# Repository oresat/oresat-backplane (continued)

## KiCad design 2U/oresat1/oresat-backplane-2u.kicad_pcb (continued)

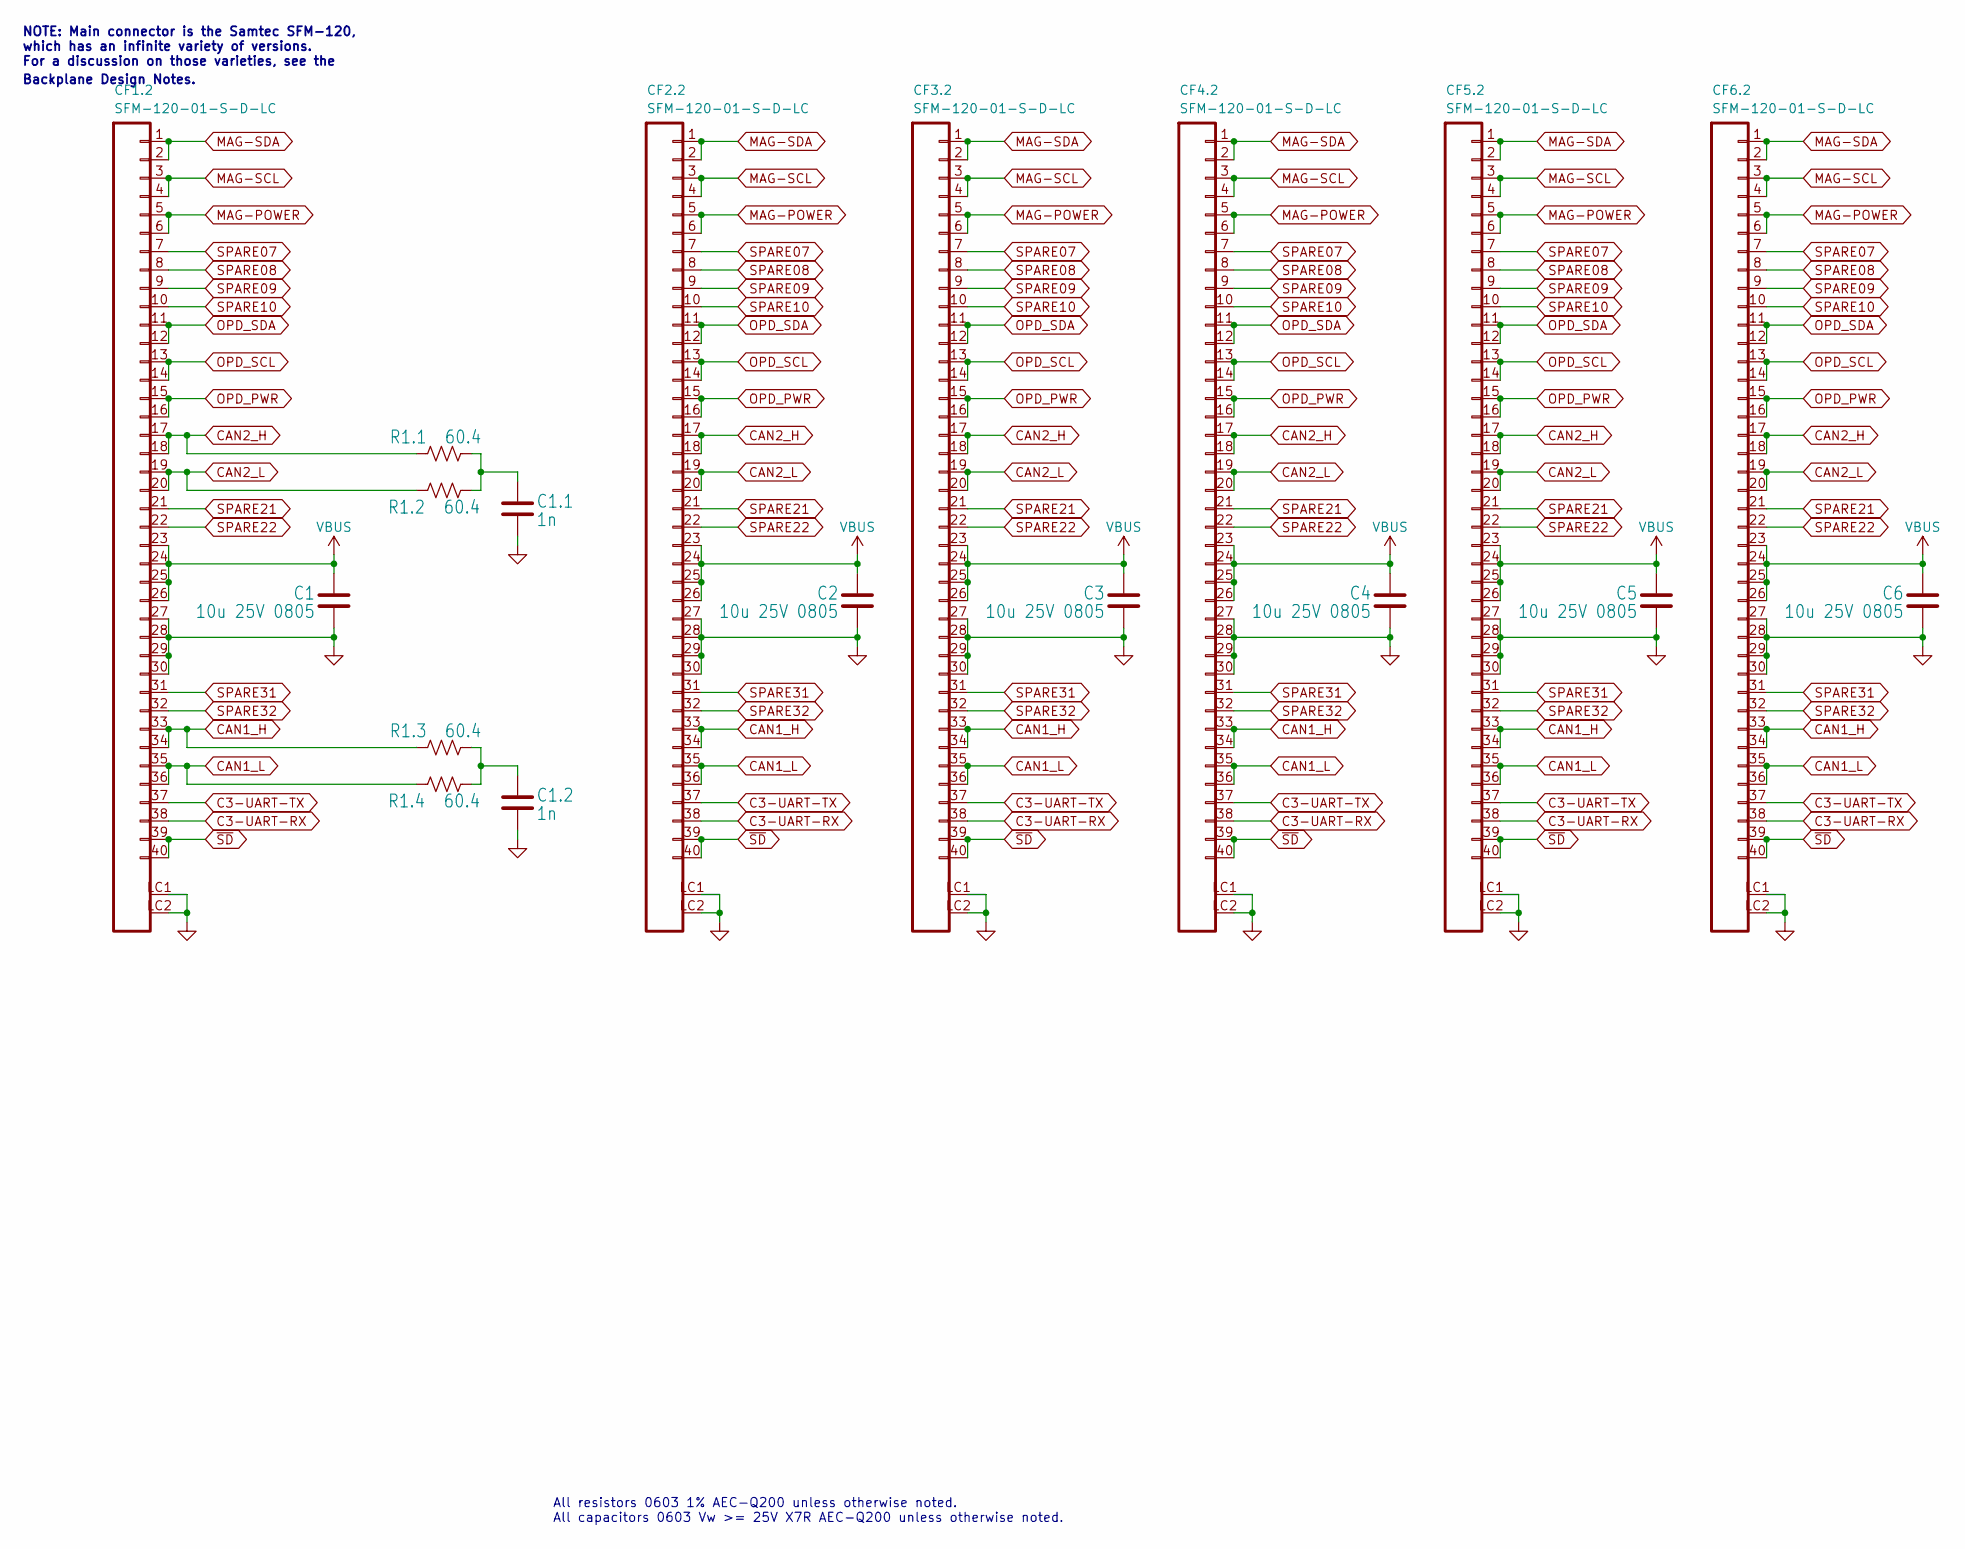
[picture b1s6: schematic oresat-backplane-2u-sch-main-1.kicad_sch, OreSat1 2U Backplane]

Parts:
C1, C2, C3, C4, C5, C6: 10u 25V 0805; C_1206_3216Metric; MPN GRT31CR71E106KE13L
C1.1, C1.2: 1n; 0603-C-NOSILK; MPN C0603C102J5GECAUTO
CF1.2, CF2.2, CF3.2, CF4.2, CF5.2, CF6.2: SFM-120-01-S-D-LC; J-SAMTEC-SFM-120-X1-XXX-D; MPN SFM-120-01-S-D-LC
R1.1, R1.2, R1.3, R1.4: 60.4; R_1206_3216Metric; MPN RMCF1206FT60R4

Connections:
C3-UART-RX: CF1.2.38, CF2.2.38, CF3.2.38, CF4.2.38, CF5.2.38, CF6.2.38; also elsewhere on the board
C3-UART-TX: CF1.2.37, CF2.2.37, CF3.2.37, CF4.2.37, CF5.2.37, CF6.2.37; also elsewhere on the board
CAN1_H: CF1.2.33, CF1.2.34, CF2.2.33, CF2.2.34, CF3.2.33, CF3.2.34, CF4.2.33, CF4.2.34, CF5.2.33, CF5.2.34, CF6.2.33, CF6.2.34, R1.3.2; also elsewhere on the board
CAN1_L: CF1.2.35, CF1.2.36, CF2.2.35, CF2.2.36, CF3.2.35, CF3.2.36, CF4.2.35, CF4.2.36, CF5.2.35, CF5.2.36, CF6.2.35, CF6.2.36, R1.4.1; also elsewhere on the board
CAN2_H: CF1.2.17, CF1.2.18, CF2.2.17, CF2.2.18, CF3.2.17, CF3.2.18, CF4.2.17, CF4.2.18, CF5.2.17, CF5.2.18, CF6.2.17, CF6.2.18, R1.1.2; also elsewhere on the board
CAN2_L: CF1.2.19, CF1.2.20, CF2.2.19, CF2.2.20, CF3.2.19, CF3.2.20, CF4.2.19, CF4.2.20, CF5.2.19, CF5.2.20, CF6.2.19, CF6.2.20, R1.2.1; also elsewhere on the board
GND: C1.2, C1.1.2, C1.2.2, C2.2, C3.2, C4.2, C5.2, C6.2, CF1.2.27, CF1.2.28, CF1.2.29, CF1.2.30, CF1.2.LC1, CF1.2.LC2, CF2.2.27, CF2.2.28, CF2.2.29, CF2.2.30, CF2.2.LC1, CF2.2.LC2, CF3.2.27, CF3.2.28, CF3.2.29, CF3.2.30, CF3.2.LC1, CF3.2.LC2, CF4.2.27, CF4.2.28, CF4.2.29, CF4.2.30, CF4.2.LC1, CF4.2.LC2, CF5.2.27, CF5.2.28, CF5.2.29, CF5.2.30, CF5.2.LC1, CF5.2.LC2, CF6.2.27, CF6.2.28, CF6.2.29, CF6.2.30, CF6.2.LC1, CF6.2.LC2; also elsewhere on the board
MAG-POWER: CF1.2.5, CF1.2.6, CF2.2.5, CF2.2.6, CF3.2.5, CF3.2.6, CF4.2.5, CF4.2.6, CF5.2.5, CF5.2.6, CF6.2.5, CF6.2.6; also elsewhere on the board
MAG-SCL: CF1.2.3, CF1.2.4, CF2.2.3, CF2.2.4, CF3.2.3, CF3.2.4, CF4.2.3, CF4.2.4, CF5.2.3, CF5.2.4, CF6.2.3, CF6.2.4; also elsewhere on the board
MAG-SDA: CF1.2.1, CF1.2.2, CF2.2.1, CF2.2.2, CF3.2.1, CF3.2.2, CF4.2.1, CF4.2.2, CF5.2.1, CF5.2.2, CF6.2.1, CF6.2.2; also elsewhere on the board
unnamed: C1.1.1, R1.1.1, R1.2.2
unnamed: C1.2.1, R1.3.1, R1.4.2
OPD_PWR: CF1.2.15, CF1.2.16, CF2.2.15, CF2.2.16, CF3.2.15, CF3.2.16, CF4.2.15, CF4.2.16, CF5.2.15, CF5.2.16, CF6.2.15, CF6.2.16; also elsewhere on the board
OPD_SCL: CF1.2.13, CF1.2.14, CF2.2.13, CF2.2.14, CF3.2.13, CF3.2.14, CF4.2.13, CF4.2.14, CF5.2.13, CF5.2.14, CF6.2.13, CF6.2.14; also elsewhere on the board
OPD_SDA: CF1.2.11, CF1.2.12, CF2.2.11, CF2.2.12, CF3.2.11, CF3.2.12, CF4.2.11, CF4.2.12, CF5.2.11, CF5.2.12, CF6.2.11, CF6.2.12; also elsewhere on the board
SPARE07: CF1.2.7, CF2.2.7, CF3.2.7, CF4.2.7, CF5.2.7, CF6.2.7; also elsewhere on the board
SPARE08: CF1.2.8, CF2.2.8, CF3.2.8, CF4.2.8, CF5.2.8, CF6.2.8; also elsewhere on the board
SPARE09: CF1.2.9, CF2.2.9, CF3.2.9, CF4.2.9, CF5.2.9, CF6.2.9; also elsewhere on the board
SPARE10: CF1.2.10, CF2.2.10, CF3.2.10, CF4.2.10, CF5.2.10, CF6.2.10; also elsewhere on the board
SPARE21: CF1.2.21, CF2.2.21, CF3.2.21, CF4.2.21, CF5.2.21, CF6.2.21; also elsewhere on the board
SPARE22: CF1.2.22, CF2.2.22, CF3.2.22, CF4.2.22, CF5.2.22, CF6.2.22; also elsewhere on the board
SPARE31: CF1.2.31, CF2.2.31, CF3.2.31, CF4.2.31, CF5.2.31, CF6.2.31; also elsewhere on the board
SPARE32: CF1.2.32, CF2.2.32, CF3.2.32, CF4.2.32, CF5.2.32, CF6.2.32; also elsewhere on the board
VBUS: C1.1, C2.1, C3.1, C4.1, C5.1, C6.1, CF1.2.23, CF1.2.24, CF1.2.25, CF1.2.26, CF2.2.23, CF2.2.24, CF2.2.25, CF2.2.26, CF3.2.23, CF3.2.24, CF3.2.25, CF3.2.26, CF4.2.23, CF4.2.24, CF4.2.25, CF4.2.26, CF5.2.23, CF5.2.24, CF5.2.25, CF5.2.26, CF6.2.23, CF6.2.24, CF6.2.25, CF6.2.26; also elsewhere on the board
~SD: CF1.2.39, CF1.2.40, CF2.2.39, CF2.2.40, CF3.2.39, CF3.2.40, CF4.2.39, CF4.2.40, CF5.2.39, CF5.2.40, CF6.2.39, CF6.2.40; also elsewhere on the board

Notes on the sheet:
NOTE: Main connector is the Samtec SFM-120, which has an infinite variety of versions. For a discussion on those varieties, see the
All resistors 0603 1% AEC-Q200 unless otherwise noted. All capacitors 0603 Vw >= 25V X7R AEC-Q200 unless otherwise noted.
Backplane Design Notes.

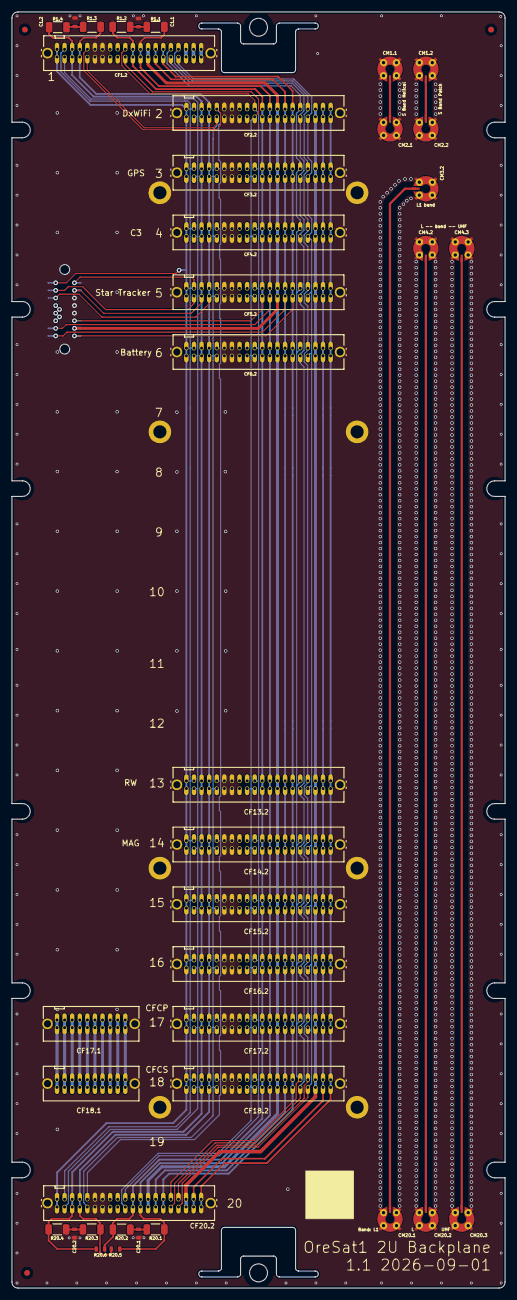
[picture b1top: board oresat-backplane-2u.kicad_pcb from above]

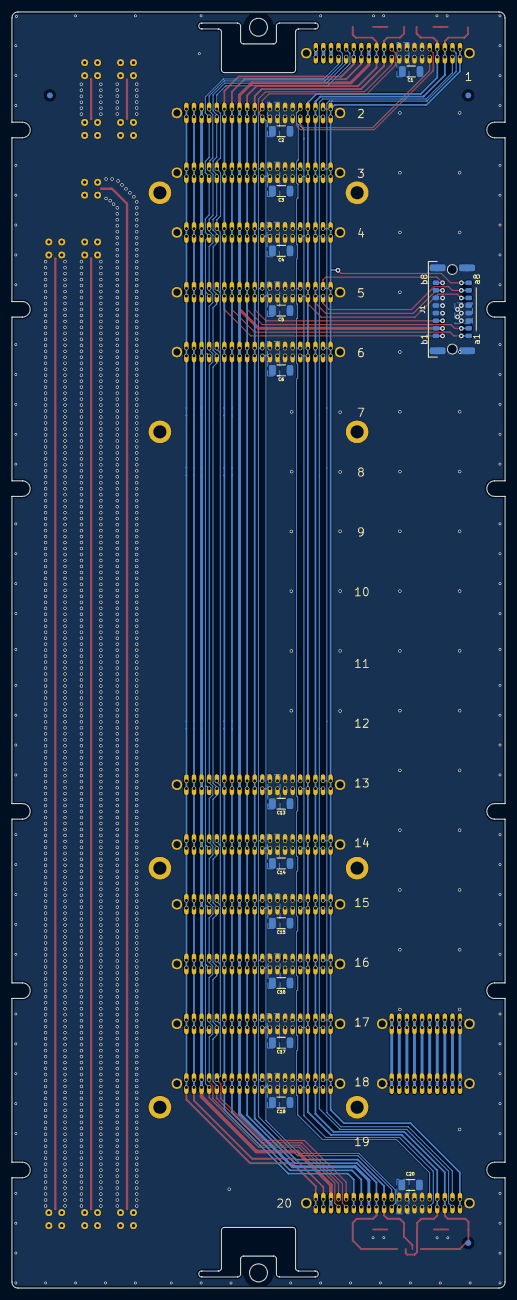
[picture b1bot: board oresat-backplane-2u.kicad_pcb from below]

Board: 4 copper layers, 82.5 x 213.5 mm, 69 parts (17 on the bottom side), 42 nets.

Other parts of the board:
PH1, PH2: MountingHole_3mm

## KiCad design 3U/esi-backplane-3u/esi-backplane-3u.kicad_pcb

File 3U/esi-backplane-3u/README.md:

---
title: "**ESI/OreSat 3U Backplane Fabrication and Assembly Information**"
subtitle: |
  **Fabrication and Assembly Information**\
  For build TIME-STAMP
fontsize: 10pt
geometry:
  - margin=0.5in
toc: true
toc-depth: 2
colorlinks: true
urlcolor: blue
---

\newpage

# About this Board

## Board Description

The ESI/OreSat 3U Backplane is the backplane for a 3U backplane based on the open source [OreSat CubeSat system](https://www.oresat.org/). The backplane has:

- 40 pin main connnectors for Oresat-based cards
- Bus voltage (2S Lithium Ion batteries with a Vnom of 7.2V)
- Two CAN busses for inter-card communication
- RF lines using SMPM RF connectors and microstrips
- A debug connector to carry critical lines to the outside of the CubeSat
- Four cutouts for solar module connections

## Documentation Links

- OreSat Backplane hardware Git repository: <https://github.com/oresat/oresat-backplane>
- **TODO:** Backplane Design Notes + Design Review Notes

## Documentation Files

| Filename                        | Notes                                    |
| ------------------------------- | ---------------------------------------- |
| README.pdf                      | This README file                         |
| PROJECT-NAME-outline.dxf        | Board outline (with holes) in DXF format |
| PROJECT-NAME-pcba.step          | 3D model of PCBA (with components)       |
| PROJECT-NAME-render-bot.jpg     | Render of the top of the 3D model        |
| PROJECT-NAME-render-bot.jpg     | Render of the bottom of the 3D model     |
| PROJECT-NAME-schematic.pdf      | PDF of board schematics                  |

## Contact Information

- Website: <https://www.oresat.org/>
- Email: <oresat@pdx.edu>
- Instagram: @pdxaerospace

## Board Renders

{width=50%}
{width=50%}

\newpage

# Printed Circuit Board (PCB) Fabrication Information

## Board Info

- 4 layer board
- Bounding box is 82.5 x 327.0 mm
- Board thickness is 1.59 mm (0.063 inch)
- **Important:** See Materials and Stack Up sections below

## Board Requirements

- Design Rules
    - Minimum Trace / Space design rules
       - Outer layers: 0.127 mm (5.0 mil) / 0.127 mm (5.0 mil)
       - Inner layers: 0.127 mm (5.0 mil) / 0.127 mm (5.0 mil)
    - Outer dimension router tolerance: +/- 0.254 mm (10.0 mil)
    - Hole placement tolerance: +/- 0.075 mm (3.0 mil)
    - Inner tab routed slot tolerance: +/- 0.254 mm (10.0 mil)
- Drills
   - Drill Positional Tolerance: 0.051 mm (2.0 mil)
   - Drill Size tolerance: +/- 0.064 mm (2.5 mil)
- Plated/Un-plated holes
  - There are 4 un-plated (NPT) holes
  - PTH minimum diameter: 0.254 mm (10 mil)
  - PTH minimum annulus: 0.102 mm (4 mil) radius
- Outline/Routing
  - Requires a 1.0 mm or smaller diameter routing bit
- Slots
  - There are no slots (although two cutouts have slot-like features)
- Cutouts
  - There are five cutouts.
- There are 3 fiducials on the top layer and 3 fiducials on the bottom layer.
- Panel tabs ("mouse bites")
   - Card edges must be smooth; no mouse bites or other intrusions into the card outline.
   - If external mouse bites are required, minimize and customer will remove by hand before assembly.
- If not otherwise specified, build to IPC 6012 Class 2 or better.

## Materials

- Controlled impedance
   - The stackup is critical for the performance of high speed signals on this board.
   - As long as the stackup is controlled, the board is not considered controlled impedance.
- Isola FR408HR or material with equivalent Dk.
- Board Surface treatment should be ENIG, althogh immersion Silver is acceptable.
- White silkscreen on top and bottom surface
- Taiyo PSR-4000 or equivalent soldermask on top and bottom, no requirements for color.

## Stack Up

| Layer         | Thickness           | Notes                                        |
|---------------|---------------------|----------------------------------------------|
| Top Copper    | 0.043 mm /  1.7 mil |  Layer 1 foil, 1 oz Cu after plating         |
| prepreg       | 0.200 mm /  7.9 mil |  Prepreg - Isola FR408HR 2113                |
| Layer 2       | 0.018 mm /  0.7 mil |  Layer 2 foil, 0.5 oz Cu                     |
| Core          | 0.991 mm /   39 mil |  Core Isola FR408HR                          |
| Layer 3       | 0.018 mm /  0.7 mil |  Layer 3 foil, 0.5 oz Cu                     |
| prepreg       | 0.200 mm /  7.9 mil |  Prepreg - Isola FR408HR 2113                |
| Bottom Copper | 0.043 mm /  1.7 mil |  Layer 4 foil, 1 oz copper after plating     |
| **Total Stackup** | **1.588 mm / 62.5 mil** |                                      |

## Array / Panel Information

- Coordinate with Contract Manufacturer (CM) for optimal size of this panel.
- If no feedback from CM, then produce single boards (no panel).

## Fabrication Files

### IPC-2581 File

| Filename                 | Notes                                   |
| ------------------------ | --------------------------------------- |
| PROJECT-NAME-ipc2581.xml | IPC-2581 board information file         |

### Legacy PCB Files

| Filename                      | Notes                                         |
| ------------------------------| --------------------------------------------- |
| PROJECT-NAME-Edge_Cuts.gbr    | RS274X file for the dimension (outline) layer |
| PROJECT-NAME-F_Silkscreen.gbr | RS274X file for the top silkscreen            |
| PROJECT-NAME-F_Mask.gbr       | RS274X file for the top soldermask            |
| PROJECT-NAME-F_Cu.gbr         | RS274X file for the top copper layer          |
| PROJECT-NAME-In1_Cu.gbr       | RS274X file for the layer 2 copper            |
| PROJECT-NAME-In2_Cu.gbr       | RS274X file for the layer 3 copper            |
| PROJECT-NAME-B_Cu.gbr         | RS274X file for the bottom copper layer       |
| PROJECT-NAME-B_Mask.gbr       | RS274X file for the bottom soldermask         |
| PROJECT-NAME-B_Silkscreen.gbr | RS274X file for the bottom silkscreen         |
| PROJECT-NAME-NPTH.drl         | Excellon file for non-plated through holes    |
| PROJECT-NAME-PTH.drl          | Excellon file for plated through holes        | 

\newpage

# Printed Circuit Board Assembly (PCBA) Information

## Assembly Info

- There are components on the top and bottom sides of the board.
- This PCBA is a mix of surface mount (SMT) and through hole (THT) components.

## Assembly Requirements

- Assemble to IPC Class 2 or better
- Bake components that are not moisture sealed to appropriate levels as required.
- Solder paste MUST be leaded.
- Aqueous flux and wash strongly preferred.
   - Clean to NASA Standard "Visibly Clean (VC)": No particles or residues are visible to the naked eye.
- No conformal coating.
- Ship in antistatic protective bag.

## Component Specific Assembly Information

- SMPM connectors (CM*.*) should be hand-added before reflow.
- Not all connectors are placed, see BOM.

## Assembly Files

### IPC-2581 File

| Filename                 | Notes                           |
| ------------------------ | ------------------------------- |
| PROJECT-NAME-ipc2581.xml | IPC-2581 board information file |

### Bill of Materials (BOM)

| Filename             | Description                            |
| -------------------- | -------------------------------------- |
| PROJECT-NAME-bom.csv | BOM in Comma Separated Variable format |

### Solder Paste Stencils

| Filename                 | Notes                                            |
| ------------------------ | ------------------------------------------------ |
| PROJECT-NAME-B_Paste.gbr | RS274X file for top/front solder paste stencil   |
| PROJECT-NAME-F_Paste.gbr | RS274X file for bottom/back solder paste stencil |

### Mounting/Placement Location

| Filename            | Description                                 |
| ------------------- | ------------------------------------------- |
| PROJECT-NAME-3u.pos | Pick and place locations for components     |

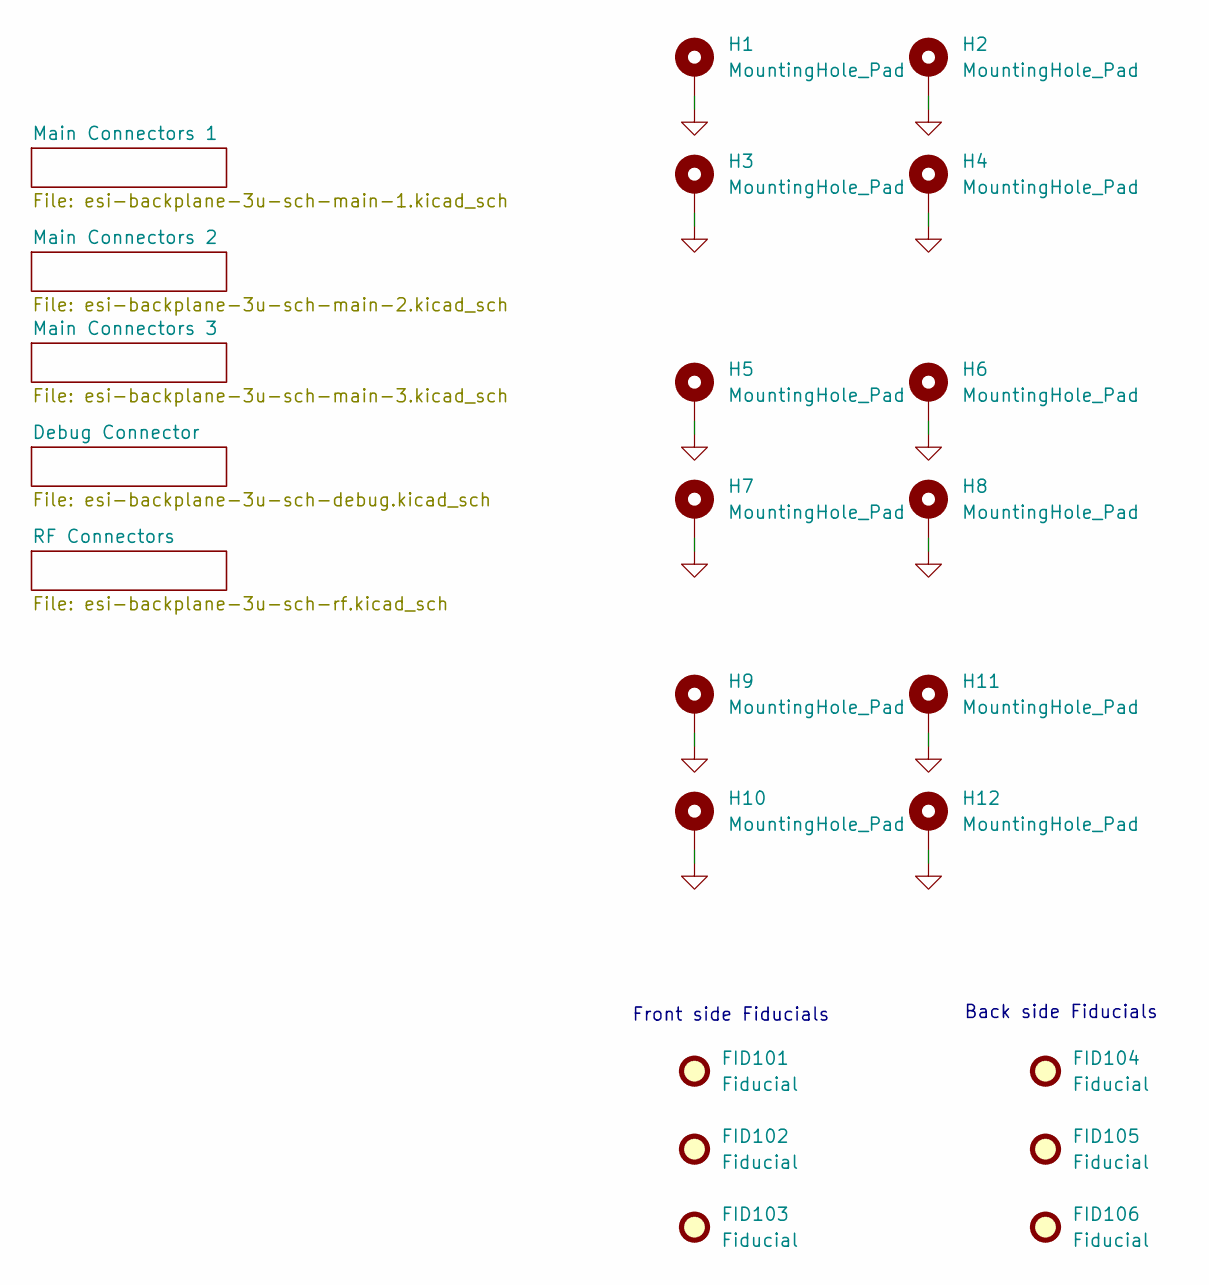
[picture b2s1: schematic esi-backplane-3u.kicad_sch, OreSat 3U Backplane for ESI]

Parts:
FID101, FID102, FID103, FID104, FID105, FID106: Fiducial; Fiducial_1mm_Mask2mm
H1, H2, H3, H4, H5, H6, H7, H8, H9, H10, H11, H12: MountingHole_Pad; MountingHole_2.2mm_M2_DIN965_Pad

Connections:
GND: H1.1, H2.1, H3.1, H4.1, H5.1, H6.1, H7.1, H8.1, H9.1, H10.1, H11.1, H12.1; also elsewhere on the board

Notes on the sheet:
Front side Fiducials
Back side Fiducials

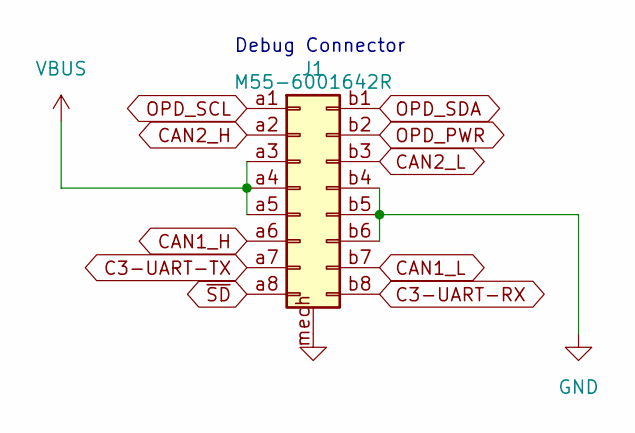
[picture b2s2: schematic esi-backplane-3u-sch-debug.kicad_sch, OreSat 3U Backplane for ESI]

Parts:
J1: M55-6001642R; m55-6001642; MPN M55-6001642R

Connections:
C3-UART-RX: J1.b8; also elsewhere on the board
C3-UART-TX: J1.a7; also elsewhere on the board
CAN1_H: J1.a6; also elsewhere on the board
CAN1_L: J1.b7; also elsewhere on the board
CAN2_H: J1.a2; also elsewhere on the board
CAN2_L: J1.b3; also elsewhere on the board
GND: J1.b4, J1.b5, J1.b6, J1.mech; also elsewhere on the board
OPD_PWR: J1.b2; also elsewhere on the board
OPD_SCL: J1.a1; also elsewhere on the board
OPD_SDA: J1.b1; also elsewhere on the board
VBUS: J1.a3, J1.a4, J1.a5; also elsewhere on the board
~SD: J1.a8; also elsewhere on the board

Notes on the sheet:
Debug Connector

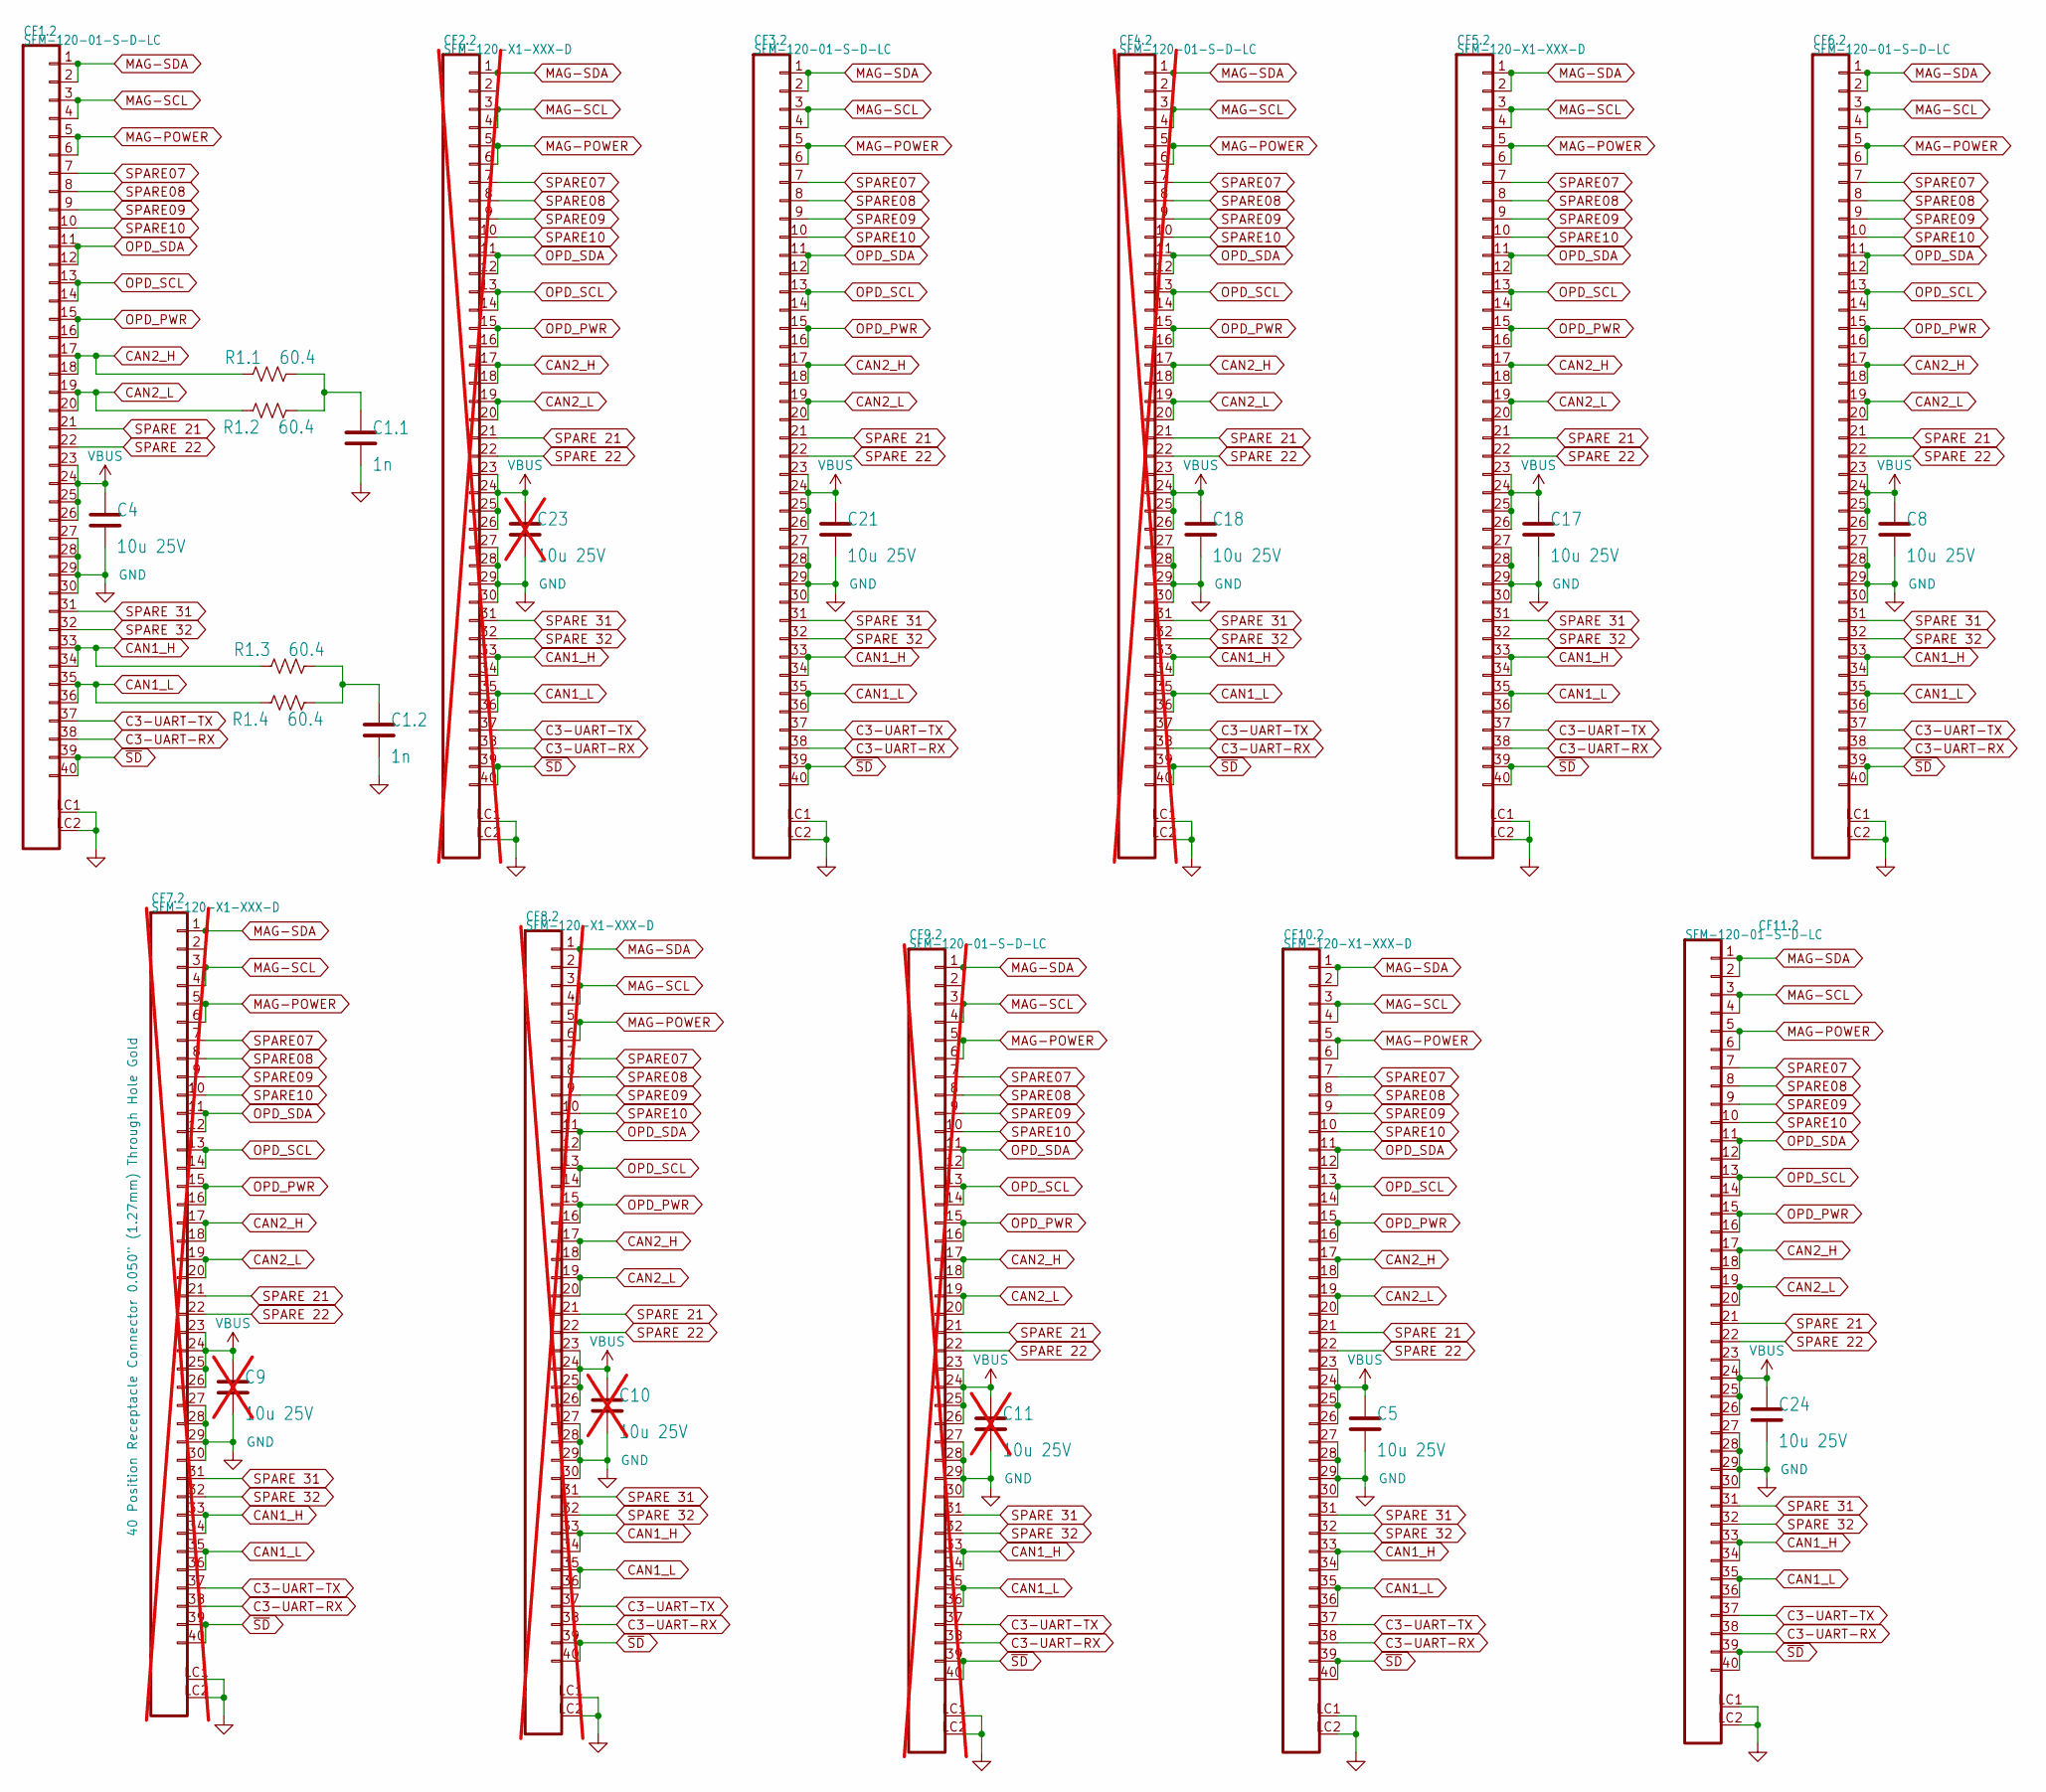
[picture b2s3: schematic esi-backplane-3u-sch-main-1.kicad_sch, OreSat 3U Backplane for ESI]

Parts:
C1.1, C1.2: 1n; 0603-C-NOSILK; MPN C0603C102J5GECAUTO
C4, C5, C8, C17, C18, C21, C24: 10u 25V; C_1206_3216Metric; MPN TMK316AB7106KLHT
C9, C10, C11, C23: 10u 25V; C_1206_3216Metric; MPN TMK316AB7106KLHT; not fitted
CF1.2, CF3.2, CF6.2, CF11.2: SFM-120-01-S-D-LC; J-SAMTEC-SFM-120-X1-XXX-D; MPN SFM-120-01-S-D-LC
CF2.2, CF7.2, CF8.2: SFM-120-X1-XXX-D; J-SAMTEC-SFM-120-X1-XXX-D; MPN SFM-120-01-S-D-LC; not fitted
CF4.2, CF9.2: SFM-120-01-S-D-LC; J-SAMTEC-SFM-120-X1-XXX-D; MPN SFM-120-01-S-D-LC; not fitted
CF5.2, CF10.2: SFM-120-X1-XXX-D; J-SAMTEC-SFM-120-X1-XXX-D; MPN SFM-120-01-S-D-LC
R1.1, R1.2, R1.3, R1.4: 60.4; R_1206_3216Metric; MPN RMCF1206FT60R4

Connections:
C3-UART-RX: CF1.2.38, CF2.2.38, CF3.2.38, CF4.2.38, CF5.2.38, CF6.2.38, CF7.2.38, CF8.2.38, CF9.2.38, CF10.2.38, CF11.2.38; also elsewhere on the board
C3-UART-TX: CF1.2.37, CF2.2.37, CF3.2.37, CF4.2.37, CF5.2.37, CF6.2.37, CF7.2.37, CF8.2.37, CF9.2.37, CF10.2.37, CF11.2.37; also elsewhere on the board
CAN1_H: CF1.2.33, CF1.2.34, CF2.2.33, CF2.2.34, CF3.2.33, CF3.2.34, CF4.2.33, CF4.2.34, CF5.2.33, CF5.2.34, CF6.2.33, CF6.2.34, CF7.2.33, CF7.2.34, CF8.2.33, CF8.2.34, CF9.2.33, CF9.2.34, CF10.2.33, CF10.2.34, CF11.2.33, CF11.2.34, R1.3.2; also elsewhere on the board
CAN1_L: CF1.2.35, CF1.2.36, CF2.2.35, CF2.2.36, CF3.2.35, CF3.2.36, CF4.2.35, CF4.2.36, CF5.2.35, CF5.2.36, CF6.2.35, CF6.2.36, CF7.2.35, CF7.2.36, CF8.2.35, CF8.2.36, CF9.2.35, CF9.2.36, CF10.2.35, CF10.2.36, CF11.2.35, CF11.2.36, R1.4.1; also elsewhere on the board
CAN2_H: CF1.2.17, CF1.2.18, CF2.2.17, CF2.2.18, CF3.2.17, CF3.2.18, CF4.2.17, CF4.2.18, CF5.2.17, CF5.2.18, CF6.2.17, CF6.2.18, CF7.2.17, CF7.2.18, CF8.2.17, CF8.2.18, CF9.2.17, CF9.2.18, CF10.2.17, CF10.2.18, CF11.2.17, CF11.2.18, R1.1.2; also elsewhere on the board
CAN2_L: CF1.2.19, CF1.2.20, CF2.2.19, CF2.2.20, CF3.2.19, CF3.2.20, CF4.2.19, CF4.2.20, CF5.2.19, CF5.2.20, CF6.2.19, CF6.2.20, CF7.2.19, CF7.2.20, CF8.2.19, CF8.2.20, CF9.2.19, CF9.2.20, CF10.2.19, CF10.2.20, CF11.2.19, CF11.2.20, R1.2.1; also elsewhere on the board
GND: C1.1.2, C1.2.2, C4.2, C5.2, C8.2, C9.2, C10.2, C11.2, C17.2, C18.2, C21.2, C23.2, C24.2, CF1.2.27, CF1.2.28, CF1.2.29, CF1.2.30, CF1.2.LC1, CF1.2.LC2, CF2.2.27, CF2.2.28, CF2.2.29, CF2.2.30, CF2.2.LC1, CF2.2.LC2, CF3.2.27, CF3.2.28, CF3.2.29, CF3.2.30, CF3.2.LC1, CF3.2.LC2, CF4.2.27, CF4.2.28, CF4.2.29, CF4.2.30, CF4.2.LC1, CF4.2.LC2, CF5.2.27, CF5.2.28, CF5.2.29, CF5.2.30, CF5.2.LC1, CF5.2.LC2, CF6.2.27, CF6.2.28, CF6.2.29, CF6.2.30, CF6.2.LC1, CF6.2.LC2, CF7.2.27, CF7.2.28, CF7.2.29, CF7.2.30, CF7.2.LC1, CF7.2.LC2, CF8.2.27, CF8.2.28, CF8.2.29, CF8.2.30, CF8.2.LC1, CF8.2.LC2, CF9.2.27, CF9.2.28, CF9.2.29, CF9.2.30, CF9.2.LC1, CF9.2.LC2, CF10.2.27, CF10.2.28, CF10.2.29, CF10.2.30, CF10.2.LC1, CF10.2.LC2, CF11.2.27, CF11.2.28, CF11.2.29, CF11.2.30, CF11.2.LC1, CF11.2.LC2; also elsewhere on the board
MAG-POWER: CF1.2.5, CF1.2.6, CF2.2.5, CF2.2.6, CF3.2.5, CF3.2.6, CF4.2.5, CF4.2.6, CF5.2.5, CF5.2.6, CF6.2.5, CF6.2.6, CF7.2.5, CF7.2.6, CF8.2.5, CF8.2.6, CF9.2.5, CF9.2.6, CF10.2.5, CF10.2.6, CF11.2.5, CF11.2.6; also elsewhere on the board
MAG-SCL: CF1.2.3, CF1.2.4, CF2.2.3, CF2.2.4, CF3.2.3, CF3.2.4, CF4.2.3, CF4.2.4, CF5.2.3, CF5.2.4, CF6.2.3, CF6.2.4, CF7.2.3, CF7.2.4, CF8.2.3, CF8.2.4, CF9.2.3, CF9.2.4, CF10.2.3, CF10.2.4, CF11.2.3, CF11.2.4; also elsewhere on the board
MAG-SDA: CF1.2.1, CF1.2.2, CF2.2.1, CF2.2.2, CF3.2.1, CF3.2.2, CF4.2.1, CF4.2.2, CF5.2.1, CF5.2.2, CF6.2.1, CF6.2.2, CF7.2.1, CF7.2.2, CF8.2.1, CF8.2.2, CF9.2.1, CF9.2.2, CF10.2.1, CF10.2.2, CF11.2.1, CF11.2.2; also elsewhere on the board
unnamed: C1.1.1, R1.1.1, R1.2.2
unnamed: C1.2.1, R1.3.1, R1.4.2
OPD_PWR: CF1.2.15, CF1.2.16, CF2.2.15, CF2.2.16, CF3.2.15, CF3.2.16, CF4.2.15, CF4.2.16, CF5.2.15, CF5.2.16, CF6.2.15, CF6.2.16, CF7.2.15, CF7.2.16, CF8.2.15, CF8.2.16, CF9.2.15, CF9.2.16, CF10.2.15, CF10.2.16, CF11.2.15, CF11.2.16; also elsewhere on the board
OPD_SCL: CF1.2.13, CF1.2.14, CF2.2.13, CF2.2.14, CF3.2.13, CF3.2.14, CF4.2.13, CF4.2.14, CF5.2.13, CF5.2.14, CF6.2.13, CF6.2.14, CF7.2.13, CF7.2.14, CF8.2.13, CF8.2.14, CF9.2.13, CF9.2.14, CF10.2.13, CF10.2.14, CF11.2.13, CF11.2.14; also elsewhere on the board
OPD_SDA: CF1.2.11, CF1.2.12, CF2.2.11, CF2.2.12, CF3.2.11, CF3.2.12, CF4.2.11, CF4.2.12, CF5.2.11, CF5.2.12, CF6.2.11, CF6.2.12, CF7.2.11, CF7.2.12, CF8.2.11, CF8.2.12, CF9.2.11, CF9.2.12, CF10.2.11, CF10.2.12, CF11.2.11, CF11.2.12; also elsewhere on the board
SPARE07: CF1.2.7, CF2.2.7, CF3.2.7, CF4.2.7, CF5.2.7, CF6.2.7, CF7.2.7, CF8.2.7, CF9.2.7, CF10.2.7, CF11.2.7; also elsewhere on the board
SPARE08: CF1.2.8, CF2.2.8, CF3.2.8, CF4.2.8, CF5.2.8, CF6.2.8, CF7.2.8, CF8.2.8, CF9.2.8, CF10.2.8, CF11.2.8; also elsewhere on the board
SPARE09: CF1.2.9, CF2.2.9, CF3.2.9, CF4.2.9, CF5.2.9, CF6.2.9, CF7.2.9, CF8.2.9, CF9.2.9, CF10.2.9, CF11.2.9; also elsewhere on the board
SPARE10: CF1.2.10, CF2.2.10, CF3.2.10, CF4.2.10, CF5.2.10, CF6.2.10, CF7.2.10, CF8.2.10, CF9.2.10, CF10.2.10, CF11.2.10; also elsewhere on the board
SPARE 21: CF1.2.21, CF2.2.21, CF3.2.21, CF4.2.21, CF5.2.21, CF6.2.21, CF7.2.21, CF8.2.21, CF9.2.21, CF10.2.21, CF11.2.21; also elsewhere on the board
SPARE 22: CF1.2.22, CF2.2.22, CF3.2.22, CF4.2.22, CF5.2.22, CF6.2.22, CF7.2.22, CF8.2.22, CF9.2.22, CF10.2.22, CF11.2.22; also elsewhere on the board
SPARE 31: CF1.2.31, CF2.2.31, CF3.2.31, CF4.2.31, CF5.2.31, CF6.2.31, CF7.2.31, CF8.2.31, CF9.2.31, CF10.2.31, CF11.2.31; also elsewhere on the board
SPARE 32: CF1.2.32, CF2.2.32, CF3.2.32, CF4.2.32, CF5.2.32, CF6.2.32, CF7.2.32, CF8.2.32, CF9.2.32, CF10.2.32, CF11.2.32; also elsewhere on the board
VBUS: C4.1, C5.1, C8.1, C9.1, C10.1, C11.1, C17.1, C18.1, C21.1, C23.1, C24.1, CF1.2.23, CF1.2.24, CF1.2.25, CF1.2.26, CF2.2.23, CF2.2.24, CF2.2.25, CF2.2.26, CF3.2.23, CF3.2.24, CF3.2.25, CF3.2.26, CF4.2.23, CF4.2.24, CF4.2.25, CF4.2.26, CF5.2.23, CF5.2.24, CF5.2.25, CF5.2.26, CF6.2.23, CF6.2.24, CF6.2.25, CF6.2.26, CF7.2.23, CF7.2.24, CF7.2.25, CF7.2.26, CF8.2.23, CF8.2.24, CF8.2.25, CF8.2.26, CF9.2.23, CF9.2.24, CF9.2.25, CF9.2.26, CF10.2.23, CF10.2.24, CF10.2.25, CF10.2.26, CF11.2.23, CF11.2.24, CF11.2.25, CF11.2.26; also elsewhere on the board
~SD: CF1.2.39, CF1.2.40, CF2.2.39, CF2.2.40, CF3.2.39, CF3.2.40, CF4.2.39, CF4.2.40, CF5.2.39, CF5.2.40, CF6.2.39, CF6.2.40, CF7.2.39, CF7.2.40, CF8.2.39, CF8.2.40, CF9.2.39, CF9.2.40, CF10.2.39, CF10.2.40, CF11.2.39, CF11.2.40; also elsewhere on the board
